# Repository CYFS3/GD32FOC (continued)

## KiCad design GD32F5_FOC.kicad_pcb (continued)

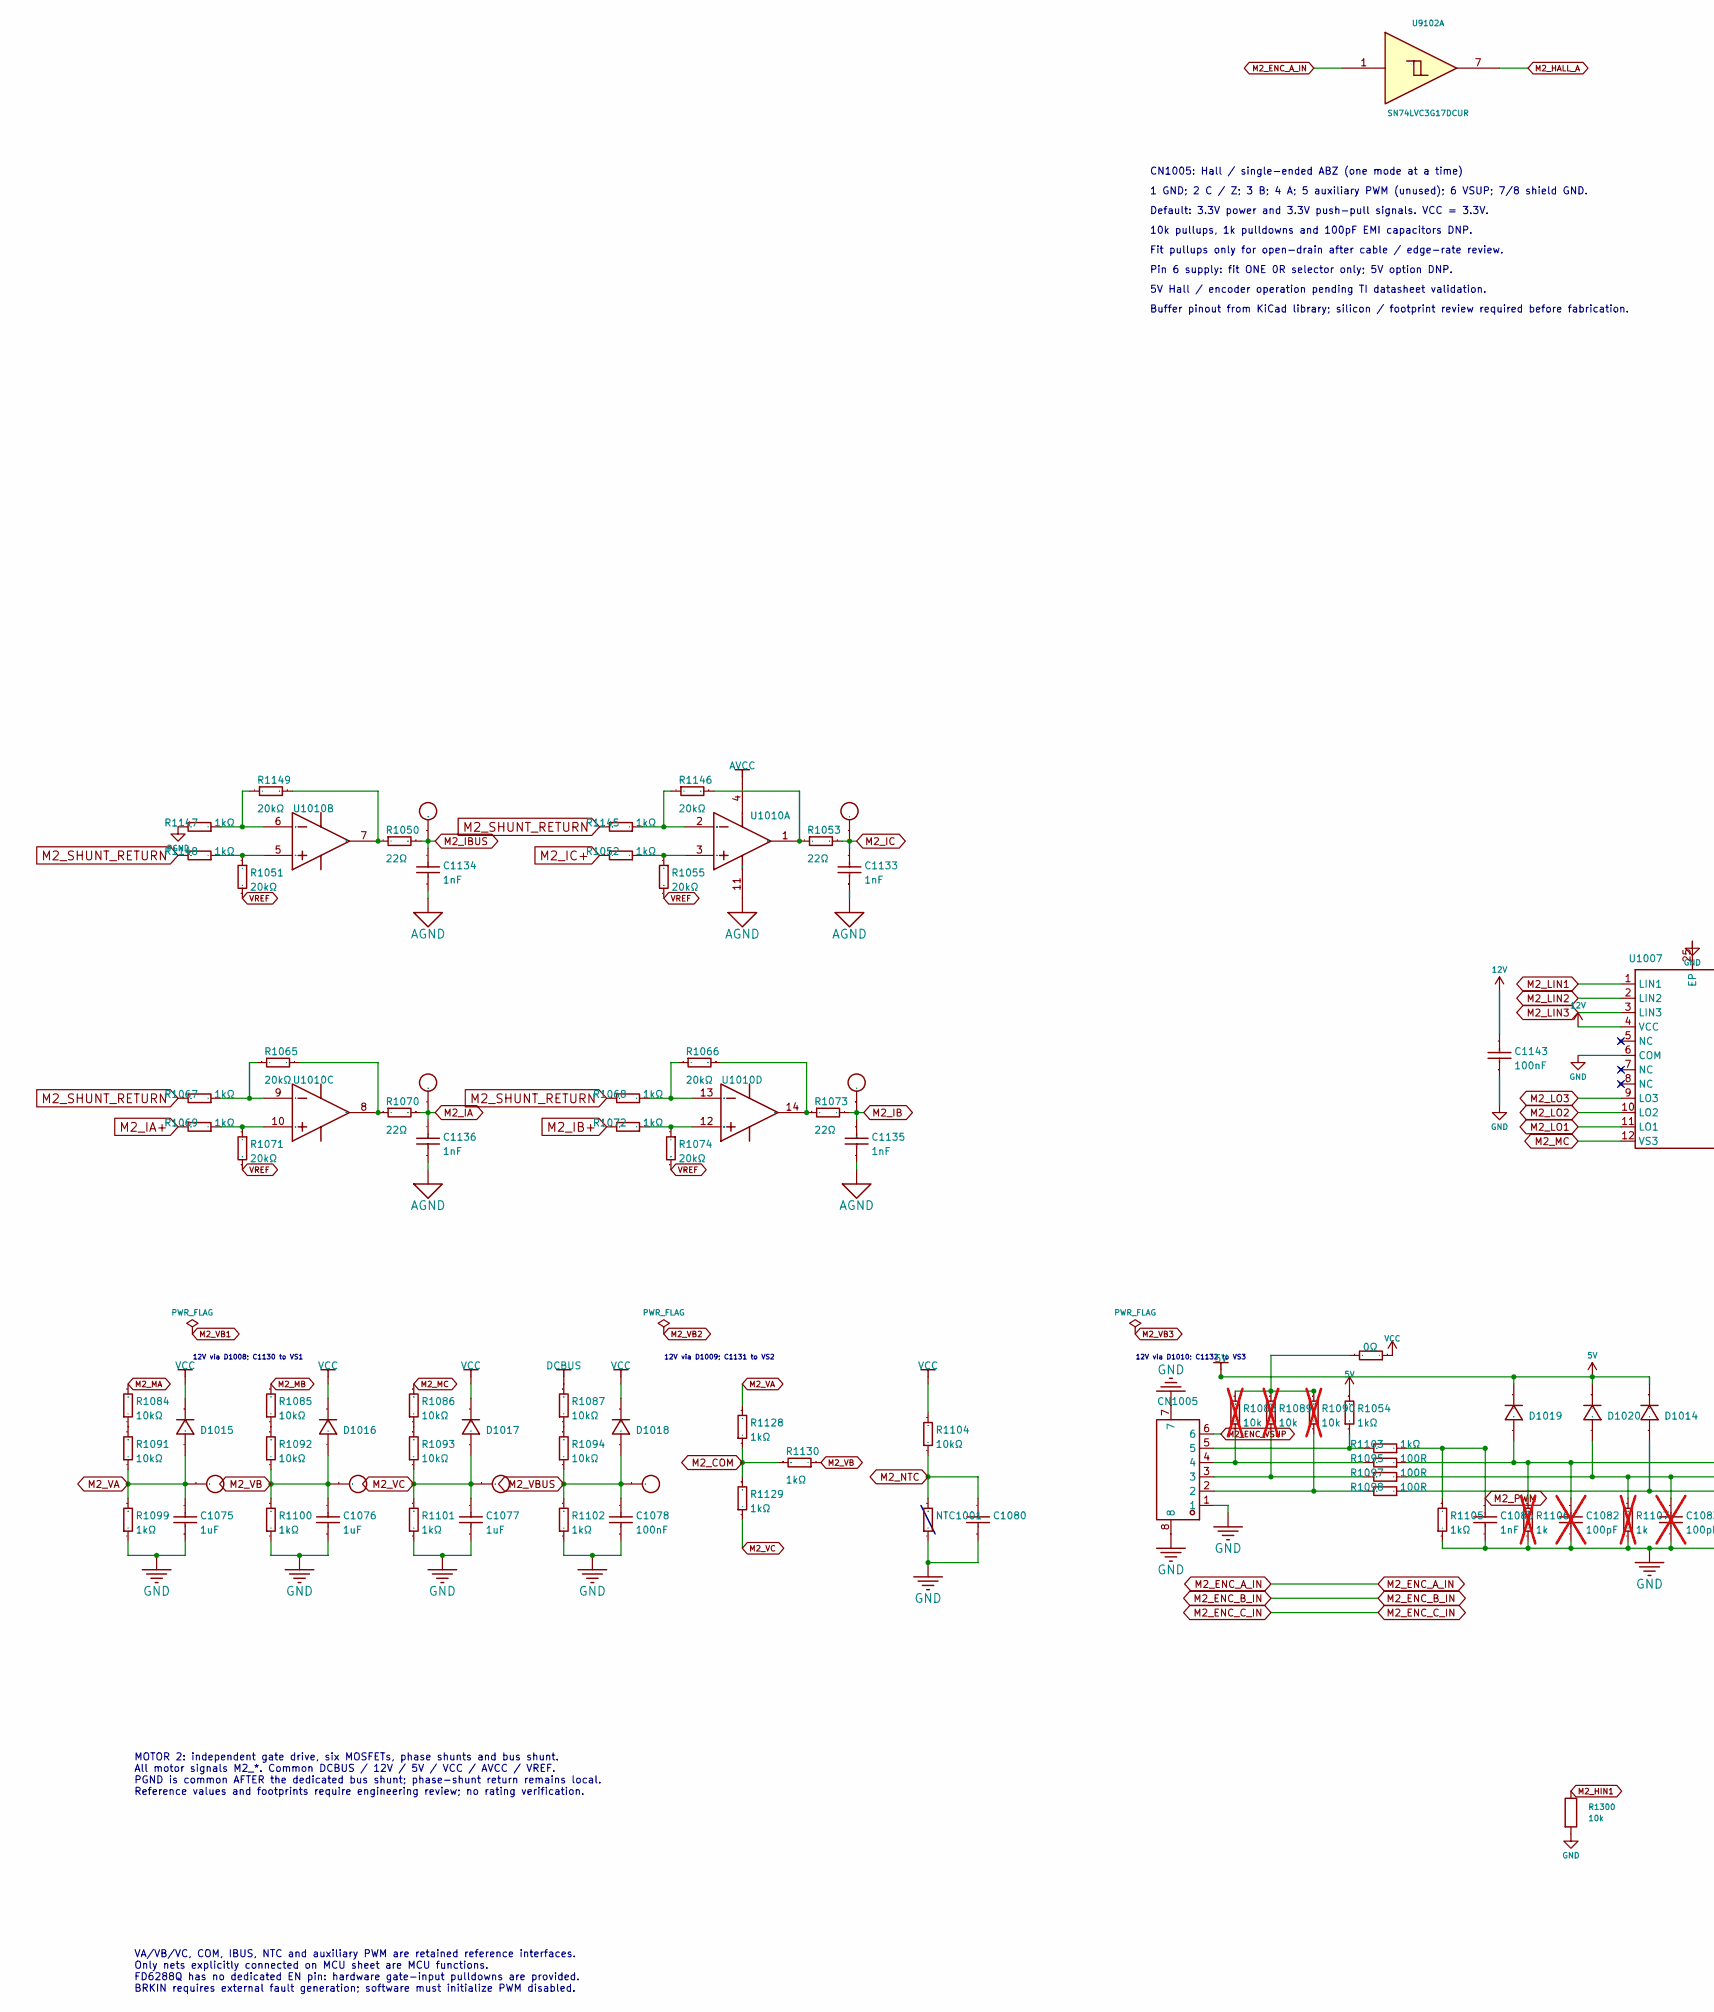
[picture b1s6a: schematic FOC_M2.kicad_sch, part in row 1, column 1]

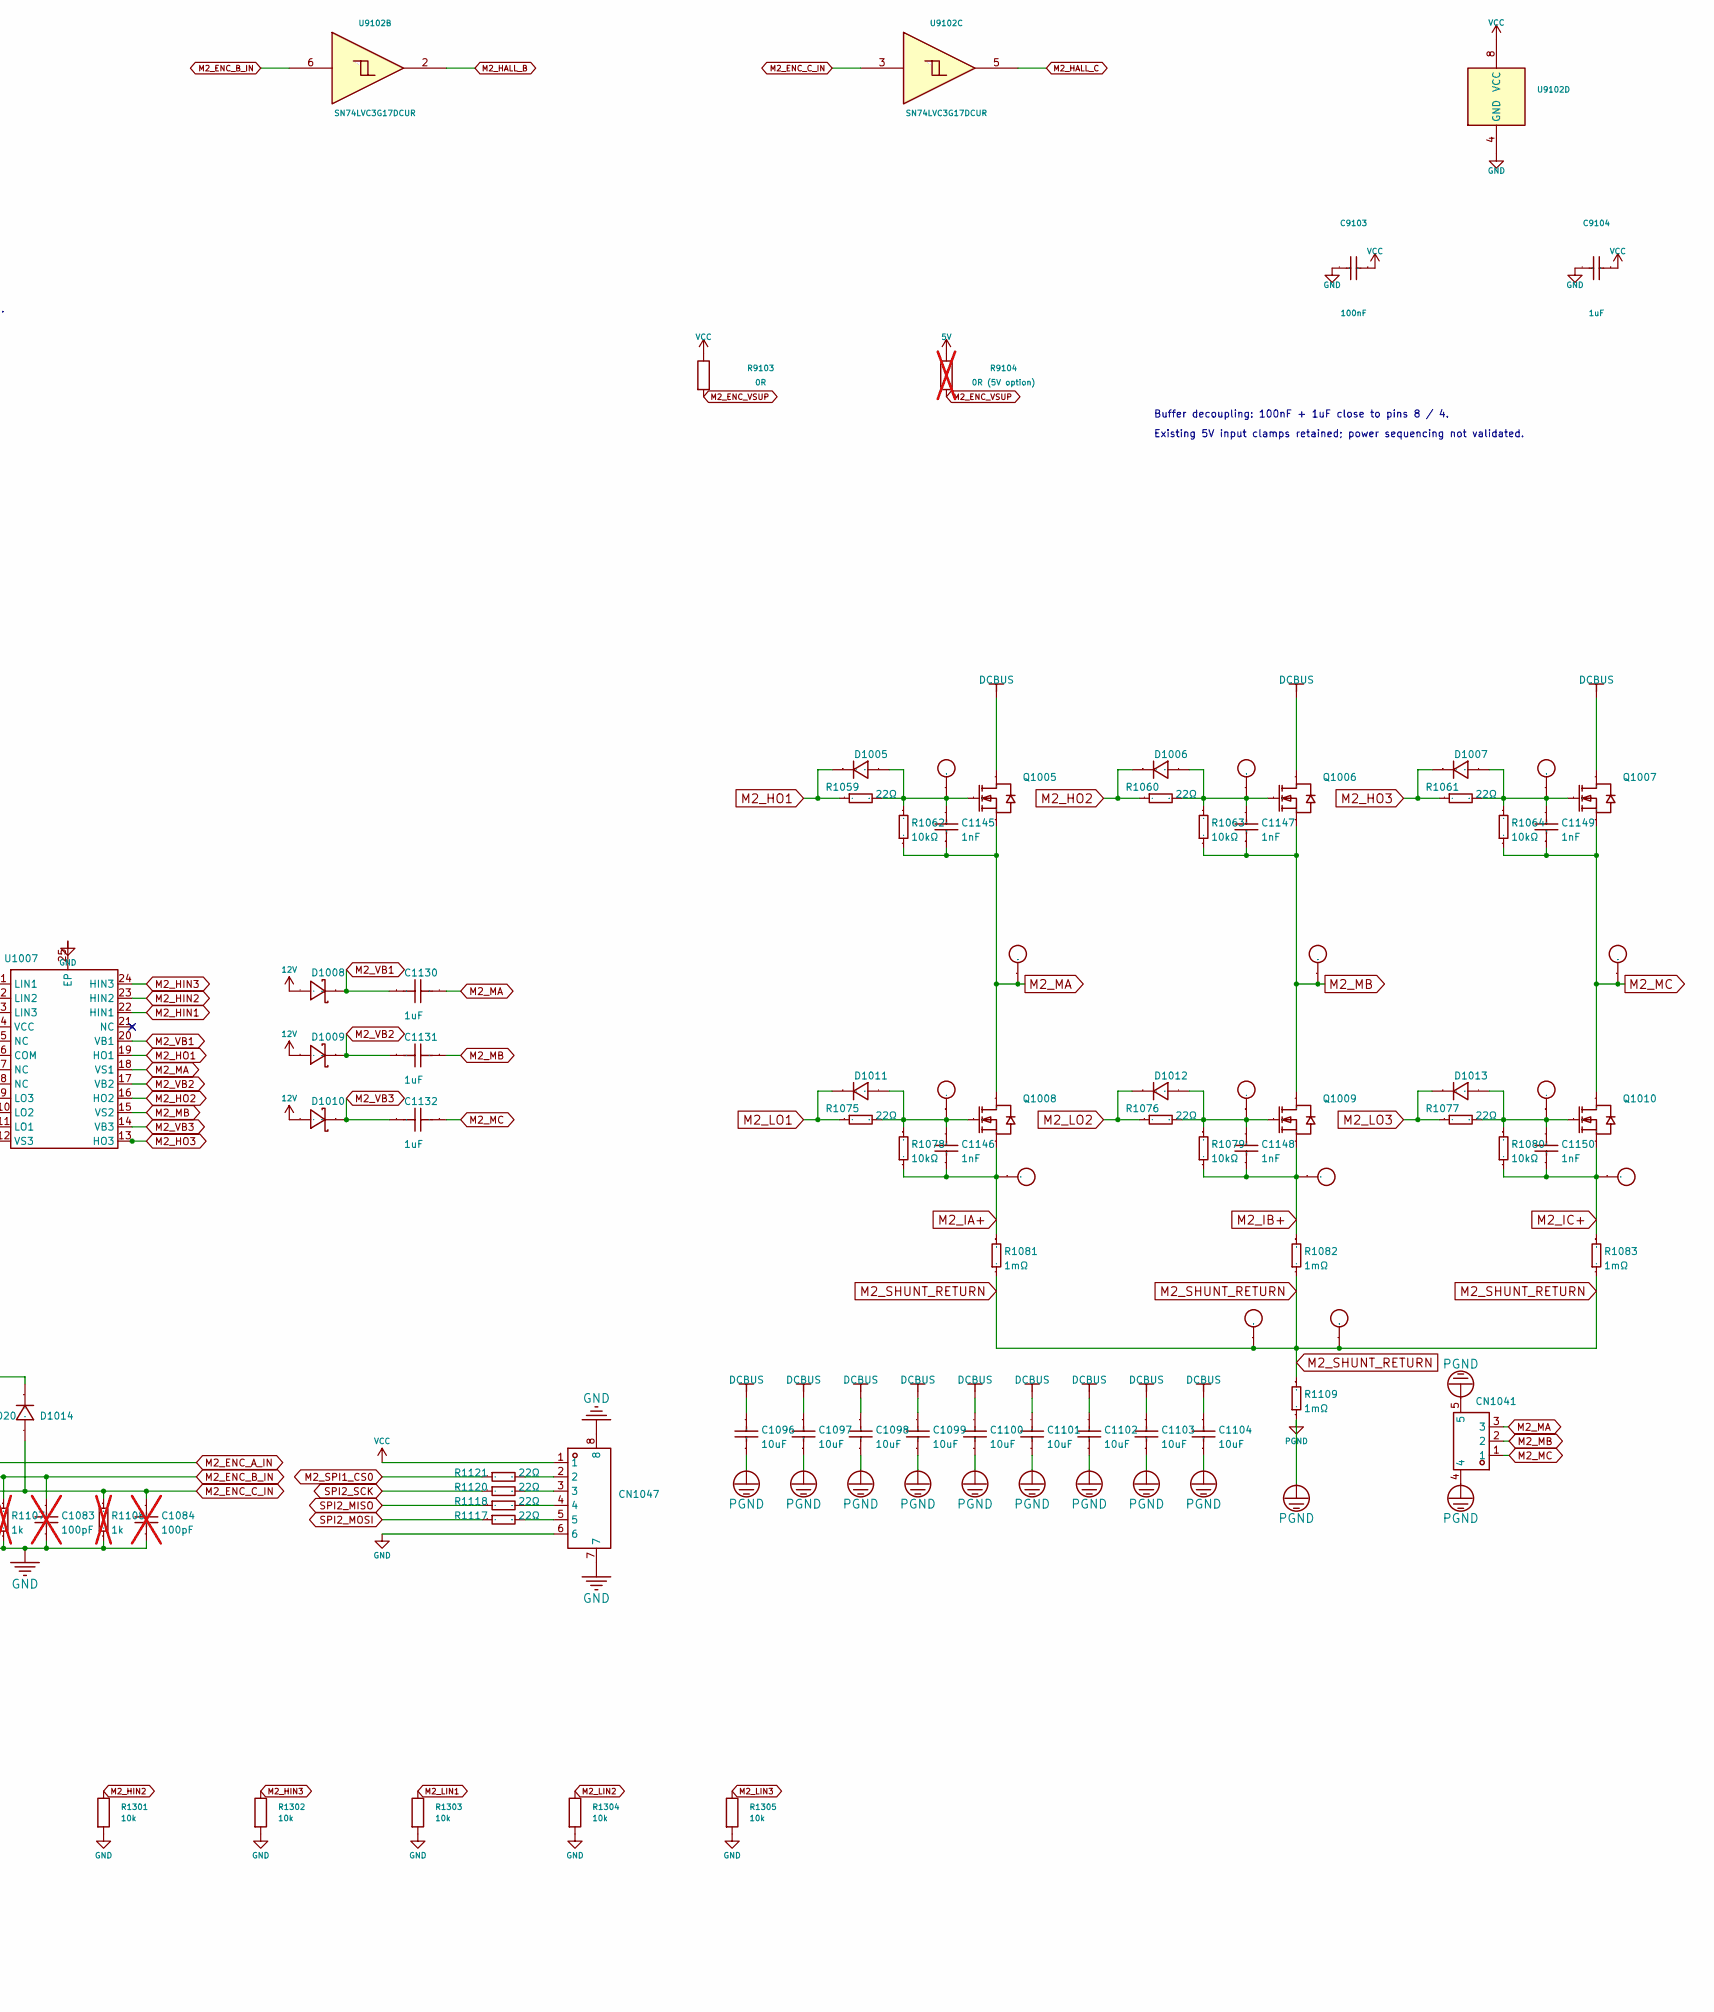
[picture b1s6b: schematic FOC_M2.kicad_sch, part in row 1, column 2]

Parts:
C1075, C1076, C1077: 1uF; C0603_S; Tolerance ±10%; Voltage Rated 50V; Manufacturer Part 0603B102K500NT; LCSC Part Name 1nF ±10% 50V
C1078, C1080: 100nF; C0603_S; Tolerance ±10%; Voltage Rated 50V; Manufacturer Part 0603B102K500NT; LCSC Part Name 1nF ±10% 50V
C1082, C1083, C1084: 100pF; C0603_S; not fitted
C1085: 1nF; C0603_S; Tolerance ±10%; Voltage Rated 50V; Manufacturer Part 0603B104K500NT; LCSC Part Name 100nF ±10% 50V
C1096, C1097, C1098, C1099, C1100, C1101, C1102, C1103, C1104: 10uF; C_1206_3216Metric; Tolerance ±10%; Voltage Rated 50V; Manufacturer Part CL31A106KBHNNNE; LCSC Part Name 10uF ±10% 50V
C1130, C1131, C1132: 1uF; C0603; Tolerance ±10%; Voltage Rating 50V; Manufacturer Part CGA0603X5R105K500JT; LCSC Part Name 1uF ±10% 50V
C1133, C1134, C1135, C1136, C1145, C1146, C1147, C1148, C1149, C1150: 1nF; C0603_S; Tolerance ±10%; Voltage Rated 50V; Manufacturer Part 0603B102K500NT; LCSC Part Name 1nF ±10% 50V
C1143: 100nF; C0603_S; Tolerance ±10%; Voltage Rated 50V; Manufacturer Part 0603B104K500NT; LCSC Part Name 100nF ±10% 50V
C9103: 100nF; C0603_S
C9104: 1uF; C0603_S
CN1005, CN1047: WAFER-GH1.25-6PWB; CONN-SMD_6P-P1.25_XUNPU_WAFER-GH1.25-6PWB; Current Rating (Max) 1A; Manufacturer Part WAFER-GH1.25-6PWB; LCSC Part Name GH1.25mm6P卧贴带扣带扣
CN1014, CN1015, CN1017, CN1018, CN1019, CN1020, CN1021, CN1022, CN1023, CN1024, CN1025, CN1026, CN1027, CN1028, CN1029, CN1030, CN1035, CN1036, CN1037, CN1038, CN1039, CN1040: TestPoint; TestPoint_D1.27_Reference; LCSC Part Name 测试点
CN1041: MR30PW-F; CONN-TH_MR30PW-F; Manufacturer Part MR30PW-F; LCSC Part Name MR30PW-F
D1005, D1006, D1007, D1011, D1012, D1013, D1014, D1015, D1016, D1017, D1018, D1019, D1020: B16WS; SOD-323_L1.8-W1.3-LS2.5-RD_2; Forward Voltage (Vf@If) 700mV@1A; Reverse Voltage (Vr) 60V; Manufacturer Part B16WS; LCSC Part Name B16WS
D1008, D1009, D1010: B16WS; D_SOD-323; Forward Voltage (Vf@If) 650mV@1A; Manufacturer Part B16WS; LCSC Part Name B16WS
NTC1001: NCP18XH103F03RB; R0603_S; Resistance Tolerance ±1%; Manufacturer Part NCP18XH103F03RB; LCSC Part Name 10kΩ 电阻精度:±1% 3380K
Q1005, Q1006, Q1007, Q1008, Q1009, Q1010: NCE7560K; Manufacturer Part NCE7560K; LCSC Part Name N沟道 75V 60A
R1049: 0Ω; R0603_S; Overload Voltage (Max) 50V; Tolerance ±1%; Manufacturer Part RS-03000FT; LCSC Part Name 0Ω ±1% 100mW
R1050, R1053, R1059, R1060, R1061, R1070, R1073, R1075, R1076, R1077, R1117, R1118, R1120, R1121: 22Ω; R0603_S; Overload Voltage (Max) 75V; Tolerance ±1%; Manufacturer Part 0603WAF220JT5E; LCSC Part Name 22Ω ±1% 100mW 厚膜电阻
R1051, R1055, R1065, R1066, R1071, R1074, R1146, R1149: 20kΩ; R0603_S; Overload Voltage (Max) 75V; Tolerance ±0.1%; Manufacturer Part RT0603BRD0720KL; LCSC Part Name 20kΩ ±0.1% 100mW
R1052, R1067, R1068, R1069, R1072, R1145, R1147, R1148: 1kΩ; R0603_S; Overload Voltage (Max) 75V; Tolerance ±0.1%; Manufacturer Part RT0603BRD071KL; LCSC Part Name 1kΩ ±0.1% 100mW
R1054, R1103, R1105, R1128, R1129, R1130: 1kΩ; R0603_S; Overload Voltage (Max) 75V; Tolerance ±1%; Manufacturer Part 0603WAF1002T5E; LCSC Part Name 10kΩ ±1% 100mW 厚膜电阻
R1062, R1063, R1064, R1078, R1079, R1080, R1104: 10kΩ; R0603_S; Overload Voltage (Max) 75V; Tolerance ±1%; Manufacturer Part 0603WAF1002T5E; LCSC Part Name 10kΩ ±1% 100mW 厚膜电阻
R1081, R1082, R1083, R1109: 1mΩ; R_2512_6332Metric
R1084, R1085, R1086, R1087, R1091, R1092, R1093, R1094: 10kΩ; R0603_S; Overload Voltage (Max) 75V; Tolerance ±1%; Manufacturer Part 0603WAF1502T5E; LCSC Part Name 15kΩ ±1% 100mW 厚膜电阻
R1088, R1089, R1090: 10k; R0603_S; not fitted
R1095, R1097, R1098: 100R; R0603_S
R1099, R1100, R1101, R1102: 1kΩ; R0603_S; Overload Voltage (Max) 75V; Tolerance ±1%; Manufacturer Part 0603WAF2001T5E; LCSC Part Name 2kΩ ±1% 100mW 厚膜电阻
R1106, R1107, R1108: 1k; R0603_S; not fitted
R1300, R1301, R1302, R1303, R1304, R1305: 10k; R_0603_1608Metric
R9103: 0R; R_0603_1608Metric
R9104: 0R (5V option); R_0603_1608Metric; not fitted
U1007: FD6288Q; QFN-24_L4.0-W4.0-P0.50-BL-EP2.6; Manufacturer Part FD6288Q; LCSC Part Name FD6288Q
U1010: RS624XQ; TSSOP-14_4.4x5mm_P0.65mm; Manufacturer Part RS624XQ; LCSC Part Name 低噪声运放RS624XQ
U9102: SN74LVC3G17DCUR; VSSOP-8_2.3x2mm_P0.5mm

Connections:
5V: D1014.1 (-), D1019.1 (-), D1020.1 (-), R1054.1, R9104.1; also elsewhere on the board
12V: C1143.2, D1008.2, D1009.2, D1010.2, U1007.4 (VCC); also elsewhere on the board
AGND: C1133.1, C1134.1, C1135.1, C1136.1, U1010.11 (V-); also elsewhere on the board
AVCC: U1010.4 (V+); also elsewhere on the board
DCBUS: C1096.2, C1097.2, C1098.2, C1099.2, C1100.2, C1101.2, C1102.2, C1103.2, C1104.2, Q1005.2 (D), Q1006.2 (D), Q1007.2 (D), R1087.1; also elsewhere on the board
GND: C1075.1, C1076.1, C1077.1, C1078.1, C1080.1, C1082.2, C1083.2, C1084.2, C1085.2, C1143.1, C9103.2, C9104.2, CN1005.1, CN1005.7, CN1005.8, CN1047.6, CN1047.7, CN1047.8, NTC1001.2, R1099.2, R1100.2, R1101.2, R1102.2, R1105.2, R1106.2, R1107.2, R1108.2, R1300.2, R1301.2, R1302.2, R1303.2, R1304.2, R1305.2, U1007.6 (COM), U1007.25 (EP), U9102.4 (GND); also elsewhere on the board
M2_COM: R1128.2, R1129.1, R1130.1
M2_ENC_A_IN: C1082.1, D1019.2 (+), R1095.2, R1106.1, U9102.1
M2_ENC_B_IN: C1083.1, D1020.2 (+), R1097.2, R1107.1, U9102.6
M2_ENC_C_IN: C1084.1, D1014.2 (+), R1098.2, R1108.1, U9102.3
M2_ENC_VSUP: CN1005.6, R9103.2, R9104.2
M2_HALL_A: U9102.7; also elsewhere on the board
M2_HALL_B: U9102.2; also elsewhere on the board
M2_HALL_C: U9102.5; also elsewhere on the board
M2_HIN1: R1300.1, U1007.22 (HIN1); also elsewhere on the board
M2_HIN2: R1301.1, U1007.23 (HIN2); also elsewhere on the board
M2_HIN3: R1302.1, U1007.24 (HIN3); also elsewhere on the board
M2_HO1: D1005.1 (-), R1059.2, U1007.19 (HO1)
M2_HO2: D1006.1 (-), R1060.2, U1007.16 (HO2)
M2_HO3: D1007.1 (-), R1061.2, U1007.13 (HO3)
M2_IA: C1136.2, CN1020.1 (1_1), R1070.1; also elsewhere on the board
M2_IA+: C1146.1, CN1028.1 (1_1), Q1008.3 (S), R1069.1, R1078.2, R1081.1
M2_IB: C1135.2, CN1021.1 (1_1), R1073.1; also elsewhere on the board
M2_IB+: C1148.1, CN1029.1 (1_1), Q1009.3 (S), R1072.1, R1079.2, R1082.1
M2_IBUS: C1134.2, CN1014.1 (1_1), R1050.1; also elsewhere on the board
M2_IC: C1133.2, CN1015.1 (1_1), R1053.1; also elsewhere on the board
M2_IC+: C1150.1, CN1030.1 (1_1), Q1010.3 (S), R1052.1, R1080.2, R1083.1
M2_LIN1: R1303.1, U1007.1 (LIN1); also elsewhere on the board
M2_LIN2: R1304.1, U1007.2 (LIN2); also elsewhere on the board
M2_LIN3: R1305.1, U1007.3 (LIN3); also elsewhere on the board
M2_LO1: D1011.1 (-), R1075.2, U1007.11 (LO1)
M2_LO2: D1012.1 (-), R1076.2, U1007.10 (LO2)
M2_LO3: D1013.1 (-), R1077.2, U1007.9 (LO3)
M2_MA: C1130.2, C1145.1, CN1022.1 (1_1), CN1041.3, Q1005.3 (S), Q1008.2 (D), R1062.2, R1084.1, U1007.18 (VS1)
M2_MB: C1131.2, C1147.1, CN1023.1 (1_1), CN1041.2, Q1006.3 (S), Q1009.2 (D), R1063.2, R1085.1, U1007.15 (VS2)
M2_MC: C1132.2, C1149.1, CN1024.1 (1_1), CN1041.1, Q1007.3 (S), Q1010.2 (D), R1064.2, R1086.1, U1007.12 (VS3)
M2_NTC: C1080.2, NTC1001.1, R1104.2; also elsewhere on the board
M2_PWM: C1085.1, R1103.2, R1105.1
M2_SHUNT_RETURN: CN1035.1 (1_1), CN1036.1 (1_1), R1067.1, R1068.1, R1081.2, R1082.2, R1083.2, R1109.1, R1145.1, R1148.1
M2_SPI1_CS0: R1121.2; also elsewhere on the board
M2_VA: C1075.2, CN1037.1 (1_1), D1015.2 (+), R1091.2, R1099.1, R1128.1
M2_VB: C1076.2, CN1038.1 (1_1), D1016.2 (+), R1092.2, R1100.1, R1130.2
M2_VB1: C1130.1, D1008.1, U1007.20 (VB1)
M2_VB2: C1131.1, D1009.1, U1007.17 (VB2)
M2_VB3: C1132.1, D1010.1, U1007.14 (VB3)
M2_VBUS: C1078.2, CN1040.1 (1_1), D1018.2 (+), R1094.2, R1102.1
M2_VC: C1077.2, CN1039.1 (1_1), D1017.2 (+), R1093.2, R1101.1, R1129.2
unnamed: CN1005.2, R1090.2, R1098.1
unnamed: CN1005.3, R1089.2, R1097.1
unnamed: CN1005.4, R1088.2, R1095.1
unnamed: CN1005.5, R1054.2, R1103.1
unnamed: CN1047.2, R1121.1
unnamed: CN1047.3, R1120.1
unnamed: CN1047.4, R1118.1
unnamed: CN1047.5, R1117.1
unnamed: C1145.2, CN1017.1 (1_1), D1005.2 (+), Q1005.1 (G), R1059.1, R1062.1
unnamed: C1147.2, CN1018.1 (1_1), D1006.2 (+), Q1006.1 (G), R1060.1, R1063.1
unnamed: C1149.2, CN1019.1 (1_1), D1007.2 (+), Q1007.1 (G), R1061.1, R1064.1
unnamed: C1146.2, CN1025.1 (1_1), D1011.2 (+), Q1008.1 (G), R1075.1, R1078.1
unnamed: C1148.2, CN1026.1 (1_1), D1012.2 (+), Q1009.1 (G), R1076.1, R1079.1
unnamed: C1150.2, CN1027.1 (1_1), D1013.2 (+), Q1010.1 (G), R1077.1, R1080.1
unnamed: R1049.1, R1088.1, R1089.1, R1090.1
unnamed: R1084.2, R1091.1
unnamed: R1085.2, R1092.1
unnamed: R1086.2, R1093.1
unnamed: R1087.2, R1094.1
unnamed: R1052.2, R1055.2, U1010.3 (+INA)
unnamed: R1145.2, R1146.2, U1010.2 (-INA)
unnamed: R1053.2, R1146.1, U1010.1 (OUTA)
unnamed: R1051.2, R1148.2, U1010.5 (+INB)
unnamed: R1147.2, R1149.2, U1010.6 (-INB)
unnamed: R1050.2, R1149.1, U1010.7 (OUTB)
unnamed: R1069.2, R1071.2, U1010.10 (+INC)
unnamed: R1065.2, R1067.2, U1010.9 (-INC)
unnamed: R1065.1, R1070.2, U1010.8 (OUTC)
unnamed: R1072.2, R1074.2, U1010.12 (+IND)
unnamed: R1066.2, R1068.2, U1010.13 (-IND)
unnamed: R1066.1, R1073.2, U1010.14 (OUTD)
PGND: C1096.1, C1097.1, C1098.1, C1099.1, C1100.1, C1101.1, C1102.1, C1103.1, C1104.1, CN1041.4, CN1041.5, R1109.2, R1147.1; also elsewhere on the board
SPI2_MISO: R1118.2; also elsewhere on the board
SPI2_MOSI: R1117.2; also elsewhere on the board
SPI2_SCK: R1120.2; also elsewhere on the board
VCC: C9103.1, C9104.1, CN1047.1, D1015.1 (-), D1016.1 (-), D1017.1 (-), D1018.1 (-), R1049.2, R1104.1, R9103.1, U9102.8 (VCC); also elsewhere on the board
VREF: R1051.1, R1055.1, R1071.1, R1074.1; also elsewhere on the board

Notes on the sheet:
VA/VB/VC, COM, IBUS, NTC and auxiliary PWM are retained reference interfaces. Only nets explicitly connected on MCU sheet are MCU functions. FD6288Q has no dedicated EN pin: hardware gate-input pulldowns are provided. BRKIN requires external fault generation; software must initialize PWM disabled.
MOTOR 2: independent gate drive, six MOSFETs, phase shunts and bus shunt. All motor signals M2_*. Common DCBUS / 12V / 5V / VCC / AVCC / VREF. PGND is common AFTER the dedicated bus shunt; phase-shunt return remains local. Reference values and footprints require engineering review; no rating verifi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
CN1005: Hall / single-ended ABZ (one mode at a time)
1 GND; 2 C / Z; 3 B; 4 A; 5 auxiliary PWM (unused); 6 VSUP; 7/8 shield GND.
Default: 3.3V power and 3.3V push-pull signals. VCC = 3.3V.
10k pullups, 1k pulldowns and 100pF EMI capacitors DNP.
Fit pullups only for open-drain after cable / edge-rate review.
Pin 6 supply: fit ONE 0R selector only; 5V option DNP.
5V Hall / encoder operation pending TI datasheet validation.
Buffer pinout from KiCad library; silicon / footprint review required before fabrication.
Buffer decoupling: 100nF + 1uF close to pins 8 / 4.
Existing 5V input clamps retained; power sequencing not validated.
12V via D1008; C1130 to VS1
12V via D1009; C1131 to VS2
12V via D1010; C1132 to VS3

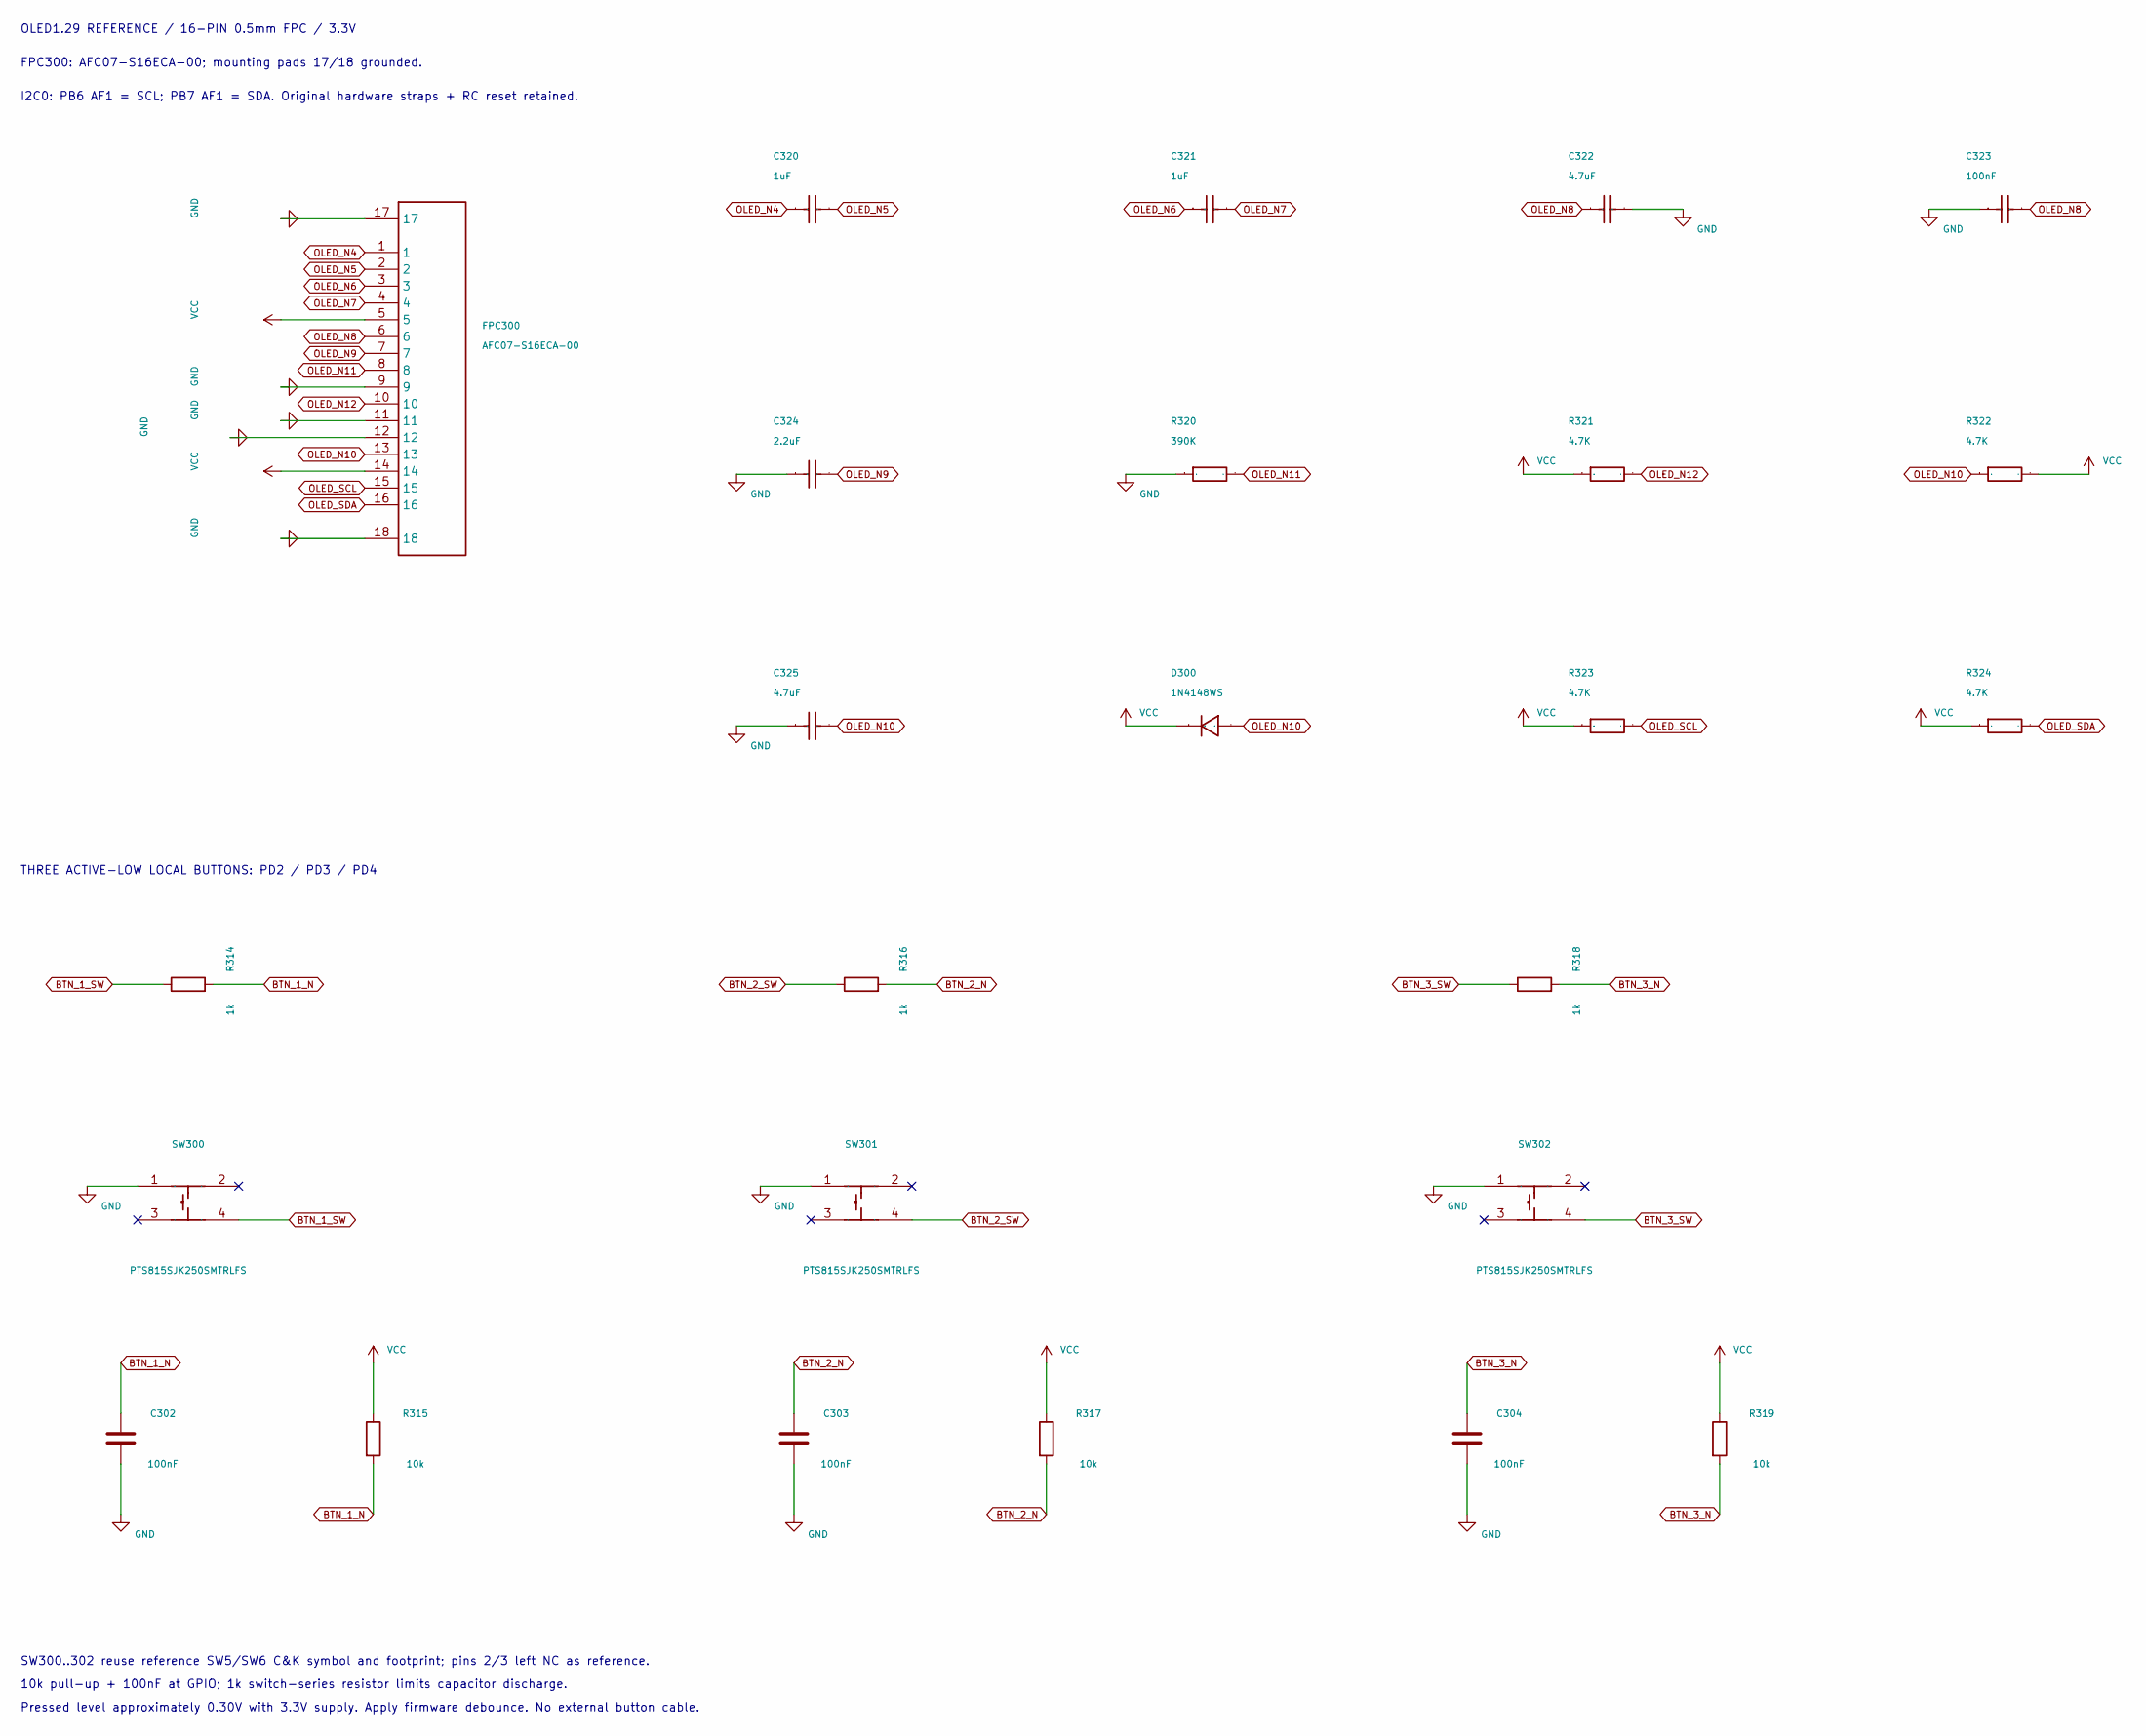
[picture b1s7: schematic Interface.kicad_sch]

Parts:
C302, C303, C304: 100nF; C_0603_1608Metric
C320, C321: 1uF; c0402-无丝印-全尺寸_2; Tolerance u00b110%; Voltage Rating 25V; Manufacturer Part CL05A105KA5NQNC; LCSC Part Name 1uF u00b110% 25V
C322, C325: 4.7uF; c0402-无丝印-全尺寸_2; Manufacturer Part CL05A106MQ5NUNC; LCSC Part Name 10uF u00b120% 6.3V
C323: 100nF; c0402-无丝印-全尺寸_2; Manufacturer Part CL05A106MQ5NUNC; LCSC Part Name 10uF u00b120% 6.3V
C324: 2.2uF; c0402-无丝印-全尺寸_2; Manufacturer Part CL05A106MQ5NUNC; LCSC Part Name 10uF u00b120% 6.3V
D300: 1N4148WS; SOD-323_L1.8-W1.3-LS2.5-RD; Manufacturer Part 1N4148WS; LCSC Part Name 100V 150mA 4ns T4
FPC300: AFC07-S16ECA-00; FPC-SMD_16P-P0.50_AFC07-S16ECA-00; Manufacturer Part AFC07-S16ECA-00; LCSC Part Name u62bdu5c49u5f0f u4e0au63a5 Pu6570:16P u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
R314, R316, R318: 1k; R_0603_1608Metric
R315, R317, R319: 10k; R_0603_1608Metric
R320: 390K; r0402-无丝印-全尺寸_1; Manufacturer Part 0402WGF1002TCE; LCSC Part Name 10ku03a9 u00b11% 62.5mW u539au819cu7535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
R321, R322, R323, R324: 4.7K; r0402-无丝印-全尺寸_1; Manufacturer Part 0402WGF1002TCE; LCSC Part Name 10ku03a9 u00b11% 62.5mW u539au819cu7535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
SW300, SW301, SW302: PTS815SJK250SMTRLFS; SW-SMD_4P-L4.2-W3.3-P2.15-LS5.1; Manufacturer Part PTS815SJK250SMTRLFS

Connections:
BTN_1_N: C302.1, R314.2, R315.2; also elsewhere on the board
BTN_1_SW: R314.1, SW300.4
BTN_2_N: C303.1, R316.2, R317.2; also elsewhere on the board
BTN_2_SW: R316.1, SW301.4
BTN_3_N: C304.1, R318.2, R319.2; also elsewhere on the board
BTN_3_SW: R318.1, SW302.4
GND: C302.2, C303.2, C304.2, C322.2, C323.1, C324.1, C325.1, FPC300.9, FPC300.11, FPC300.12, FPC300.17, FPC300.18, R320.1, SW300.1, SW301.1, SW302.1; also elsewhere on the board
OLED_N4: C320.1, FPC300.1
OLED_N5: C320.2, FPC300.2
OLED_N6: C321.1, FPC300.3
OLED_N7: C321.2, FPC300.4
OLED_N8: C322.1, C323.2, FPC300.6
OLED_N9: C324.2, FPC300.7
OLED_N10: C325.2, D300.2 (A), FPC300.13, R322.1
OLED_N11: FPC300.8, R320.2
OLED_N12: FPC300.10, R321.2
OLED_SCL: FPC300.15, R323.2; also elsewhere on the board
OLED_SDA: FPC300.16, R324.2; also elsewhere on the board
VCC: D300.1 (K), FPC300.5, FPC300.14, R315.1, R317.1, R319.1, R321.1, R322.2, R323.1, R324.1; also elsewhere on the board

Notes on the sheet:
THREE ACTIVE-LOW LOCAL BUTTONS: PD2 / PD3 / PD4
SW300..302 reuse reference SW5/SW6 C&K symbol and footprint; pins 2/3 left NC as reference.
10k pull-up + 100nF at GPIO; 1k switch-series resistor limits capacitor discharge.
Pressed level approximately 0.30V with 3.3V supply. Apply firmware debounce. No external button cable.
OLED1.29 REFERENCE / 16-PIN 0.5mm FPC / 3.3V
FPC300: AFC07-S16ECA-00; mounting pads 17/18 grounded.
I2C0: PB6 AF1 = SCL; PB7 AF1 = SDA. Original hardware straps + RC reset retained.

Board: 2 copper layers, 532 parts (33 on the bottom side), 244 nets, no tracks yet.

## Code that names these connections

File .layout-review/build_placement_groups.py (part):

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group('shared_buck12',[3,50,35,63],'U6/L6 compact switching loop; FB parts shielded from SW node.')
group('shared_buck5',[3,65,35,76],'U19/L9 compact local input/output capacitors.')
group('analog_reference',[39,63,62,74],'U12 low-noise reference distribution; keep away from buck and switching-node polygons.')
group('logic_ldo',[39,77,61,88],'U2 AVCC and U20 VCC; output capacitors at pins; R3 ground connection not a reason to cut a ground plane.')
group('mcu',[65,77,111,112],'LQFP100 including dedicated analog and digital decoupling; two crystals get local pin-based refinement.')
group('mcu_debug',[65,114,111,120],'Accessible J200/J201/TP200; rectangle may expand downward after actual connector bbox.')
group('hslink',[3,80,35,117],'USB west edge, ESD between connector and HPM. U8007 is an inductor, not IC.')
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def cluster(id,refs,owner,note):clusters.append({'id':id,'refs':[r for r in refs if r in parts],'anchor_ref':owner,'placement_rule':note})
cluster('mcu_hxtal',['Y200','C210','C211'],'U1','Pin12/13 local island, shortest symmetric tracks; no switched copper beneath oscillator island')
cluster('mcu_lxtal',['Y201','C214','C215'],'U1','Pin8/9 local island, low leakage and short loop, no digital through-routing')
cluster('mcu_vdda',['C206','C207','R203'],'U1','At pin22 with quiet AGND return')
cluster('mcu_vref',['C208','C213'],'U1','At pin21/20 with quiet return')
cluster('mcu_vbat',['C212'],'U1','At pin6, independent short decoupling loop')
for cap,pin in zip(rr('C',range(200,205)),['11','28','50','75','100']):cluster('decouple_'+cap,[cap],'U1','At actual VDD pin'+pin+'; verify pad positions and permit nearest-equivalent cap permutation')
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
